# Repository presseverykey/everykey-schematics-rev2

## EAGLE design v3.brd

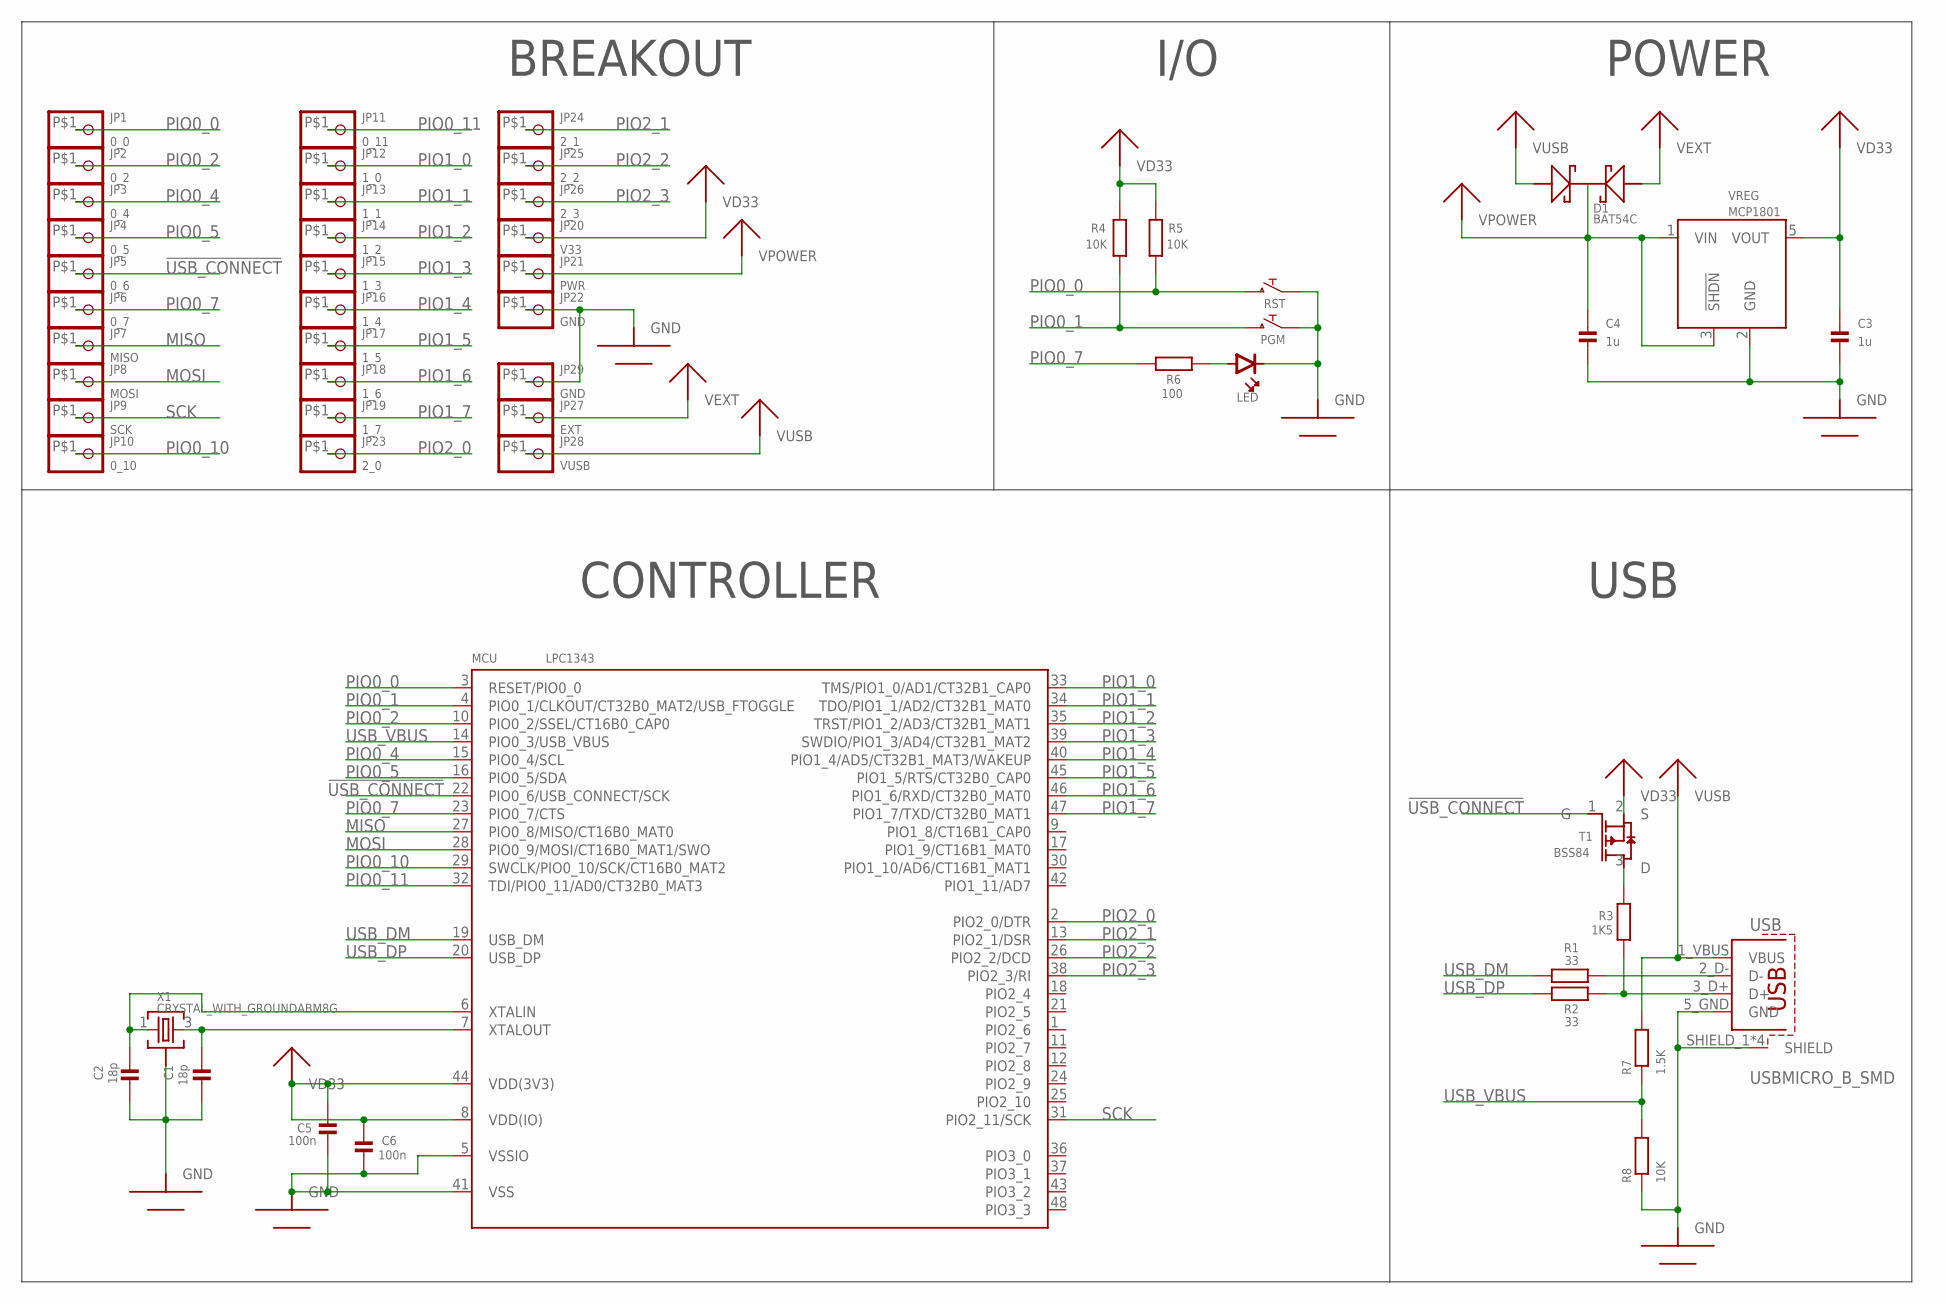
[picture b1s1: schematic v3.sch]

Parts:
C1, C2: 18p; 0603
C3, C4: 1u; 0603
C5, C6: 100n; 0603
D1: BAT54C; SOT323
JP1: 0_0; PCB_MEDIUM_RECT_PAD
JP2: 0_2; PCB_MEDIUM_RECT_PAD
JP3: 0_4; PCB_MEDIUM_RECT_PAD
JP4: 0_5; PCB_MEDIUM_RECT_PAD
JP5: 0_6; PCB_MEDIUM_RECT_PAD
JP6: 0_7; PCB_MEDIUM_RECT_PAD
JP7: MISO; PCB_MEDIUM_RECT_PAD
JP8: MOSI; PCB_MEDIUM_RECT_PAD
JP9: SCK; PCB_MEDIUM_RECT_PAD
JP10: 0_10; PCB_MEDIUM_RECT_PAD
JP11: 0_11; PCB_MEDIUM_RECT_PAD
JP12: 1_0; PCB_MEDIUM_RECT_PAD
JP13: 1_1; PCB_MEDIUM_RECT_PAD
JP14: 1_2; PCB_MEDIUM_RECT_PAD
JP15: 1_3; PCB_MEDIUM_RECT_PAD
JP16: 1_4; PCB_MEDIUM_RECT_PAD
JP17: 1_5; PCB_MEDIUM_RECT_PAD
JP18: 1_6; PCB_MEDIUM_RECT_PAD
JP19: 1_7; PCB_MEDIUM_RECT_PAD
JP20: V33; PCB_MEDIUM_RECT_PAD
JP21: PWR; PCB_MEDIUM_RECT_PAD
JP22: GND; PCB_MEDIUM_RECT_PAD
JP23: 2_0; PCB_MEDIUM_RECT_PAD
JP24: 2_1; PCB_MEDIUM_RECT_PAD
JP25: 2_2; PCB_MEDIUM_RECT_PAD
JP26: 2_3; PCB_MEDIUM_RECT_PAD
JP27: EXT; PCB_LARGER_RECT_PAD
JP28: VUSB; PCB_LARGER_RECT_PAD
JP29: GND; PCB_LARGER_RECT_PAD
LED: 0603_POLAR
MCU: LPC1343; LQFP48
PGM: PUSHBUTTONKMR2XX; CK-KMR2
R1, R2: 33; 0603
R3: 1K5; 0603
R4, R5, R8: 10K; 0603
R6: 100; 0603
R7: 1.5K; 0603
RST: PUSHBUTTONKMR2XX; CK-KMR2
T1: BSS84; SOT23
USB: USBMICRO_B_SMD; MICRO_USB_B_SMD
VREG: MCP1801; SOT-23-5
X1: CRYSTAL_WITH_GROUNDABM8G; ABM8G

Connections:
!USB_CONNECT: JP5.P$1, MCU.22 (PIO0_6/USB_CONNECT/SCK), T1.1 (G)
GND: C1.1, C2.1, C3.2, C4.2, C5.2, C6.2, JP22.P$1, JP29.P$1, LED.K (CATHODE), MCU.5 (VSSIO), MCU.41 (VSS), PGM.P$1 (1), PGM.P$2 (1), R8.1, RST.P$1 (1), RST.P$2 (1), USB.5_GND (GND), USB.SHIELD_1 (SHIELD), USB.SHIELD_2 (SHIELD), USB.SHIELD_3 (SHIELD), USB.SHIELD_4 (SHIELD), VREG.2 (GND), X1.2 (GND), X1.4 (GND)
MISO: JP7.P$1, MCU.27 (PIO0_8/MISO/CT16B0_MAT0)
MOSI: JP8.P$1, MCU.28 (PIO0_9/MOSI/CT16B0_MAT1/SWO)
unnamed: C2.2, MCU.6 (XTALIN), X1.1
unnamed: C1.2, MCU.7 (XTALOUT), X1.3 (2)
unnamed: R3.1, T1.3 (D)
unnamed: R1.1, USB.2_D- (D-)
unnamed: LED.A (ANODE), R6.1
PIO0_0: JP1.P$1, MCU.3 (RESET/PIO0_0), R5.1, RST.P$3 (2), RST.P$4 (2)
PIO0_1: MCU.4 (PIO0_1/CLKOUT/CT32B0_MAT2/USB_FTOGGLE), PGM.P$3 (2), PGM.P$4 (2), R4.1
PIO0_2: JP2.P$1, MCU.10 (PIO0_2/SSEL/CT16B0_CAP0)
PIO0_4: JP3.P$1, MCU.15 (PIO0_4/SCL)
PIO0_5: JP4.P$1, MCU.16 (PIO0_5/SDA)
PIO0_7: JP6.P$1, MCU.23 (PIO0_7/CTS), R6.2
PIO0_10: JP10.P$1, MCU.29 (SWCLK/PIO0_10/SCK/CT16B0_MAT2)
PIO0_11: JP11.P$1, MCU.32 (TDI/PIO0_11/AD0/CT32B0_MAT3)
PIO1_0: JP12.P$1, MCU.33 (TMS/PIO1_0/AD1/CT32B1_CAP0)
PIO1_1: JP13.P$1, MCU.34 (TDO/PIO1_1/AD2/CT32B1_MAT0)
PIO1_2: JP14.P$1, MCU.35 (TRST/PIO1_2/AD3/CT32B1_MAT1)
PIO1_3: JP15.P$1, MCU.39 (SWDIO/PIO1_3/AD4/CT32B1_MAT2)
PIO1_4: JP16.P$1, MCU.40 (PIO1_4/AD5/CT32B1_MAT3/WAKEUP)
PIO1_5: JP17.P$1, MCU.45 (PIO1_5/RTS/CT32B0_CAP0)
PIO1_6: JP18.P$1, MCU.46 (PIO1_6/RXD/CT32B0_MAT0)
PIO1_7: JP19.P$1, MCU.47 (PIO1_7/TXD/CT32B0_MAT1)
PIO2_0: JP23.P$1, MCU.2 (PIO2_0/DTR)
PIO2_1: JP24.P$1, MCU.13 (PIO2_1/DSR)
PIO2_2: JP25.P$1, MCU.26 (PIO2_2/DCD)
PIO2_3: JP26.P$1, MCU.38 (PIO2_3/RI)
SCK: JP9.P$1, MCU.31 (PIO2_11/SCK)
USB_D+: R2.1, R3.2, USB.3_D+ (D+)
USB_DM: MCU.19 (USB_DM), R1.2
USB_DP: MCU.20 (USB_DP), R2.2
USB_VBUS: MCU.14 (PIO0_3/USB_VBUS), R7.1, R8.2
VD33: C3.1, C5.1, C6.1, JP20.P$1, MCU.8 (VDD(IO)), MCU.44 (VDD(3V3)), R4.2, R5.2, T1.2 (S), VREG.5 (VOUT)
VEXT: D1.2 (ANODE2), JP27.P$1
VPOWER: C4.1, D1.3 (CATHODE), JP21.P$1, VREG.1 (VIN), VREG.3 (!SHDN)
VUSB: D1.1 (ANODE1), JP28.P$1, R7.2, USB.1_VBUS (VBUS)

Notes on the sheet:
POWER
USB
BREAKOUT
CONTROLLER
I/O

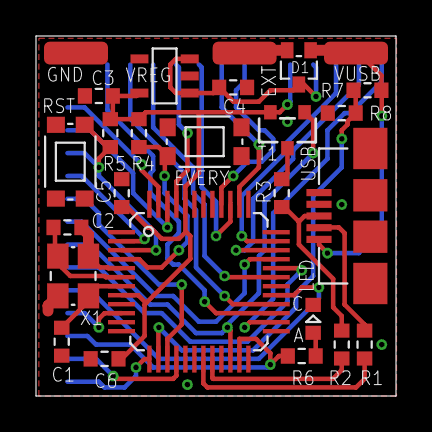
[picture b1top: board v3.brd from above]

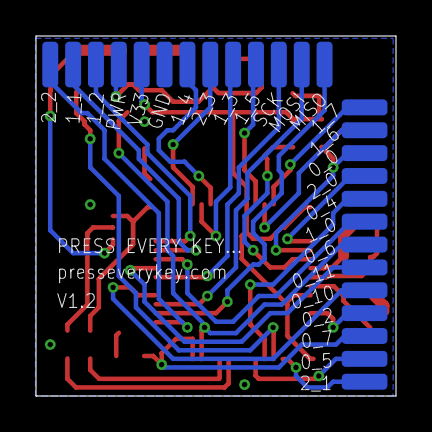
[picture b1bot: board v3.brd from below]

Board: 2 copper layers, 20.0 x 20.0 mm, 52 parts (26 on the bottom side), 38 nets.

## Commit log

2013-07-01 initial release
2015-09-28 Removed old references
2015-09-28 Fixed URL
